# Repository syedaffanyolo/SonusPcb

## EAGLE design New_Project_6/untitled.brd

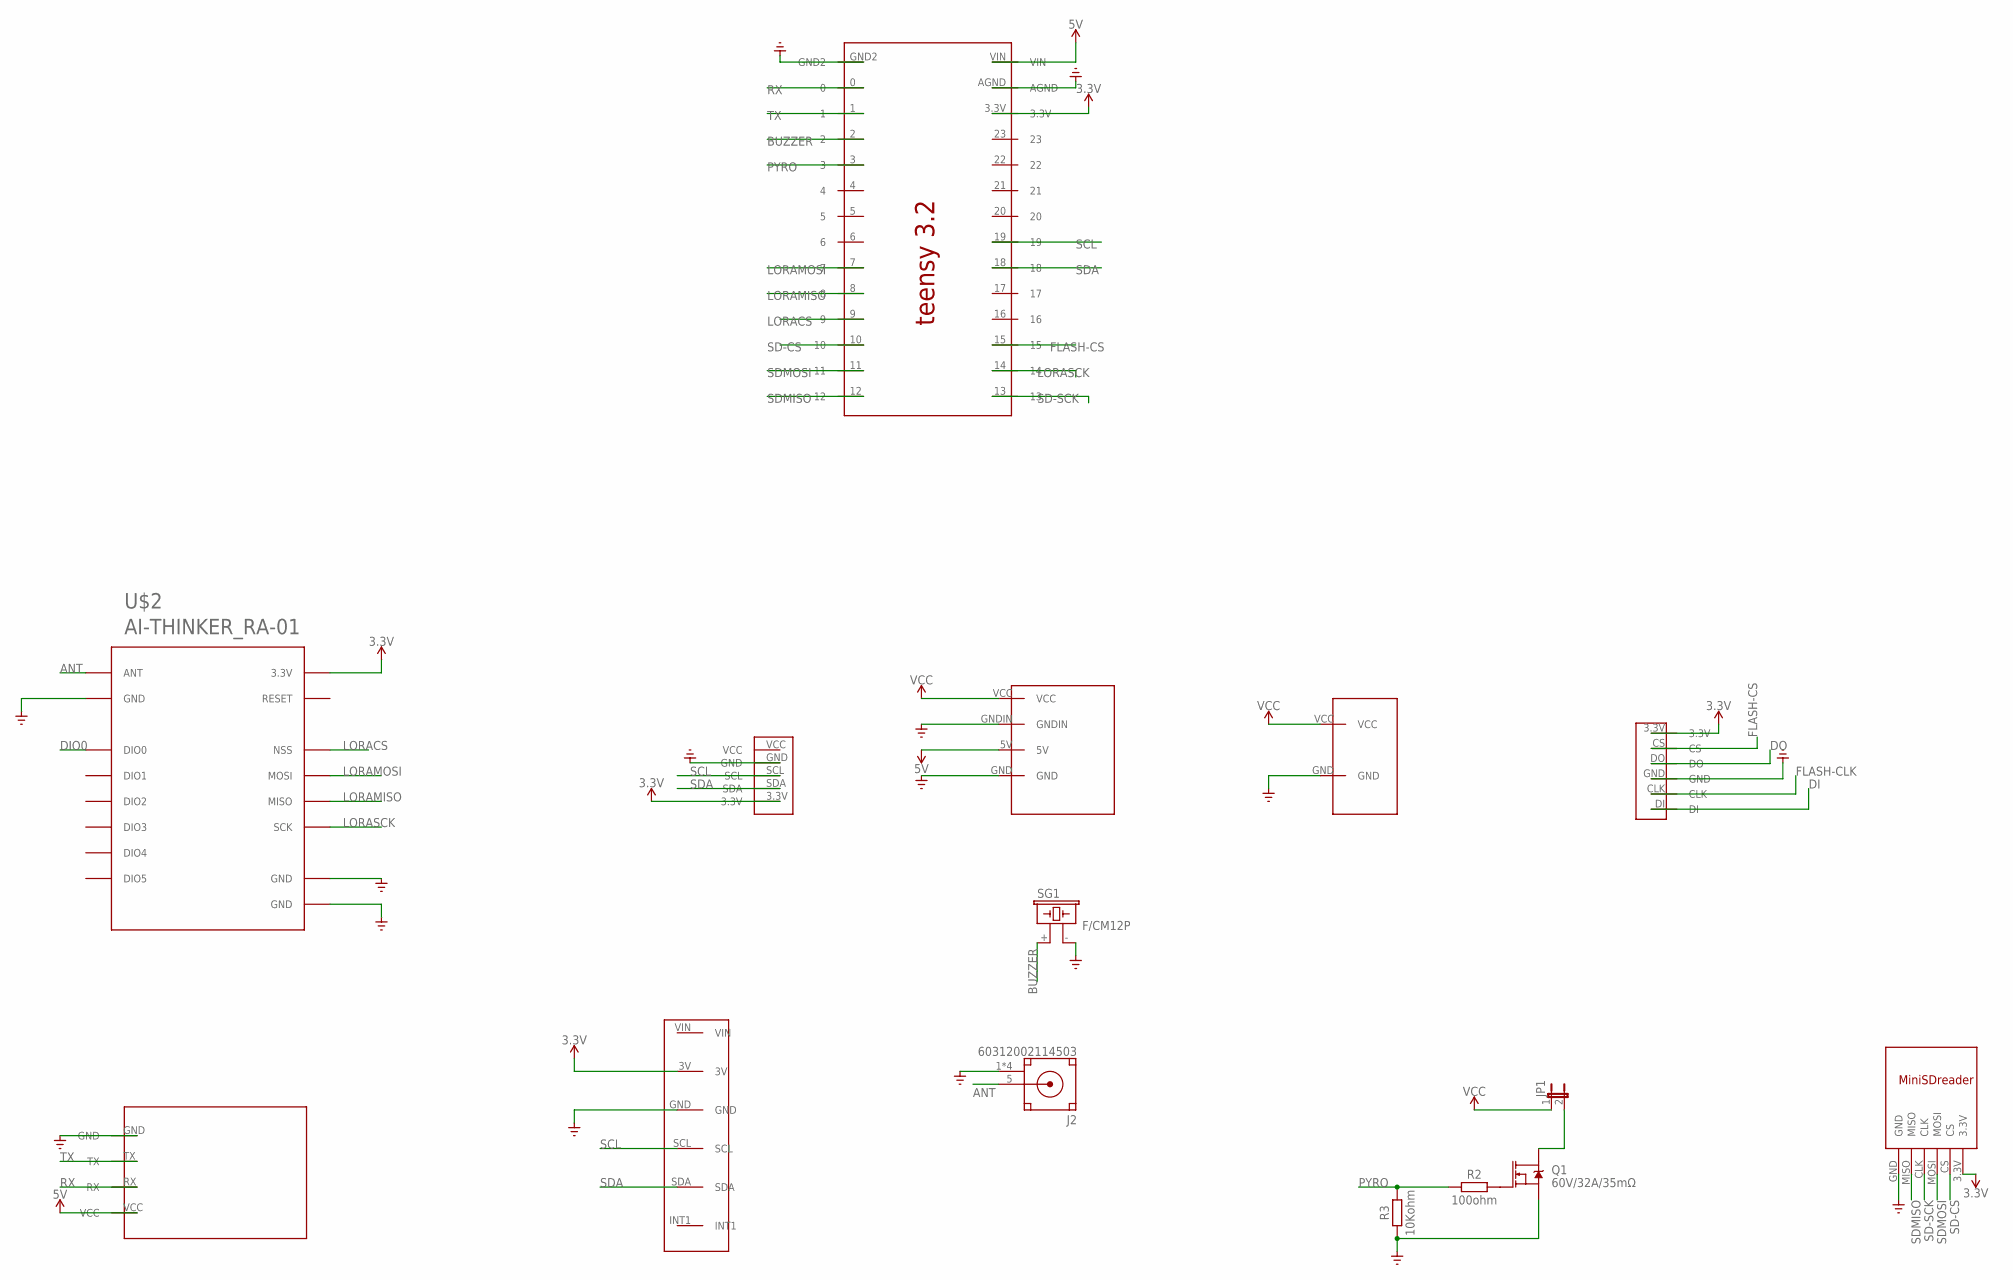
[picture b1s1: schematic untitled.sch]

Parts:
J2: 60312002114503
JP1: JP1E; JP1
Q1: 60V/32A/35mΩ; TO220V
R2: 100ohm; RESAD724W46L381D178B
R3: 10Kohm; RESAD724W46L381D178B
SG1: F/CM12P
U$1: TEENSY3.2
U$2: AI-THINKER_RA-01
U$3: BMP180
U$4: NEO-M8NGPSMODULE
U$5: ICM20649
U$6: FLASH
U$7: MINISDREADER
U$8: BATT
U$9: VREG

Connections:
3.3V: U$1.3.3V, U$2.P$3 (3.3V), U$3.3.3V, U$5.3V, U$6.3.3V, U$7.3.3V
5V: U$1.VIN, U$4.VCC, U$9.5V
ANT: J2.5 (SIGNAL), U$2.P$1 (ANT)
BUZZER: SG1.+ (1), U$1.2
DI: U$6.DI
DIO0: U$2.P$5 (DIO0)
DO: U$6.DO
FLASH-CLK: U$6.CLK
FLASH-CS: U$1.15, U$6.CS
GND: J2.1 (GND), J2.2 (GND), J2.3 (GND), J2.4 (GND), Q1.3 (S), R3.1, SG1.- (2), U$1.AGND, U$1.GND2, U$2.P$2 (GND), U$2.P$9 (GND), U$2.P$16 (GND), U$3.GND, U$4.GND, U$5.GND, U$6.GND, U$7.GND, U$8.GND, U$9.GND, U$9.GNDIN
LORACS: U$1.9, U$2.P$15 (NSS)
LORAMISO: U$1.8, U$2.P$13 (MISO)
LORAMOSI: U$1.7, U$2.P$14 (MOSI)
LORASCK: U$1.14, U$2.P$12 (SCK)
unnamed: JP1.2, Q1.2 (D)
unnamed: Q1.1 (G), R2.2
PYRO: R2.1, R3.2, U$1.3
RX: U$1.0, U$4.RX
SCL: U$1.19, U$3.SCL, U$5.SCL
SD-CS: U$1.10, U$7.CS
SD-SCK: U$1.13, U$7.CLK
SDA: U$1.18, U$3.SDA, U$5.SDA
SDMISO: U$1.12, U$7.MISO
SDMOSI: U$1.11, U$7.MOSI
TX: U$1.1, U$4.TX
VCC: JP1.1, U$8.VCC, U$9.VCC

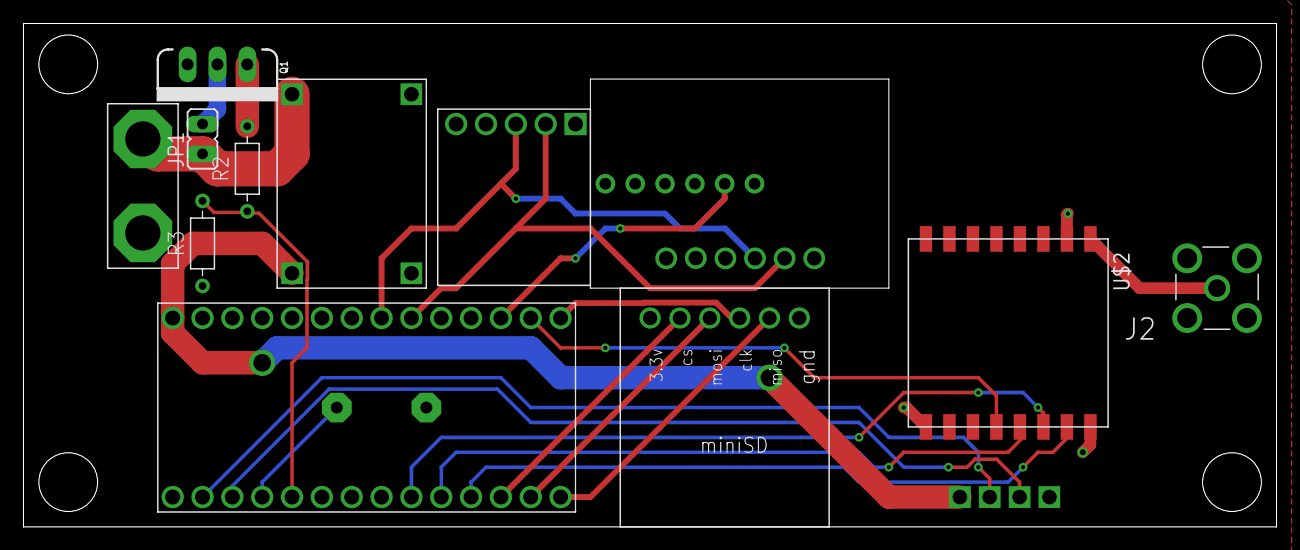
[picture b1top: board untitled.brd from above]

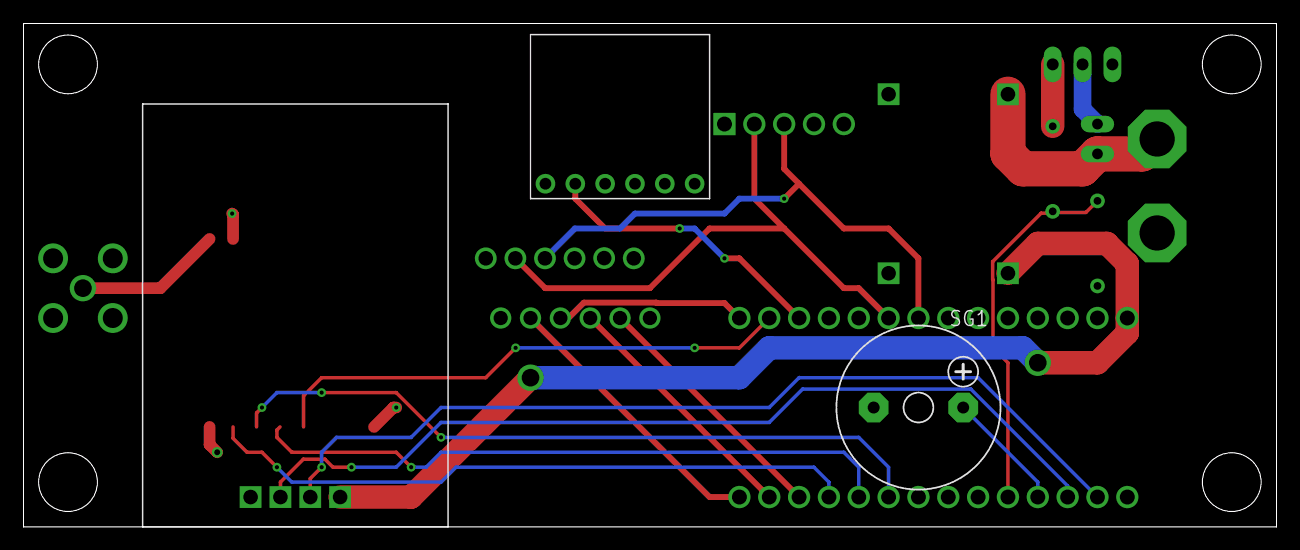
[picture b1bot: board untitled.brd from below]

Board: 2 copper layers, 106.7 x 42.9 mm, 15 parts (3 on the bottom side), 22 nets.

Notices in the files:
parts and their libraries:
SparkFun-DiscreteSemi: Licensing: Creative Commons ShareAlike 4.0 International - https://creativecommons.org/licenses/by-sa/4.0
